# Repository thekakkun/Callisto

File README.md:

# Callisto

Callisto is a digital clock that uses a Russian IV-18 vacuum fluorescent tube for the display. The clock uses an ESP32 to automatically sync time.

The name *Callisto* was chosen so that the name could be displayed on an 8-digit seven-segment display.

## Features:
- Sync time, retrieved using WiFi
- Automatically switch to daylight saving time
- Clock display settings configured using web browser
- Automatic shutoff during night hours in order to decrease energy usage and extend tube life
- Auto-dimming based on ambient light conditions

## Special thanks

The software and hardware design of the clock was ~~stolen from~~ heavily inspired by the following projects:

- [Ice Tube Clock by Lady Ada](https://learn.adafruit.com/ice-tube-clock-kit/)
- [Flora-ESP8266 by mcer12](https://github.com/mcer12/Flora-ESP8266)

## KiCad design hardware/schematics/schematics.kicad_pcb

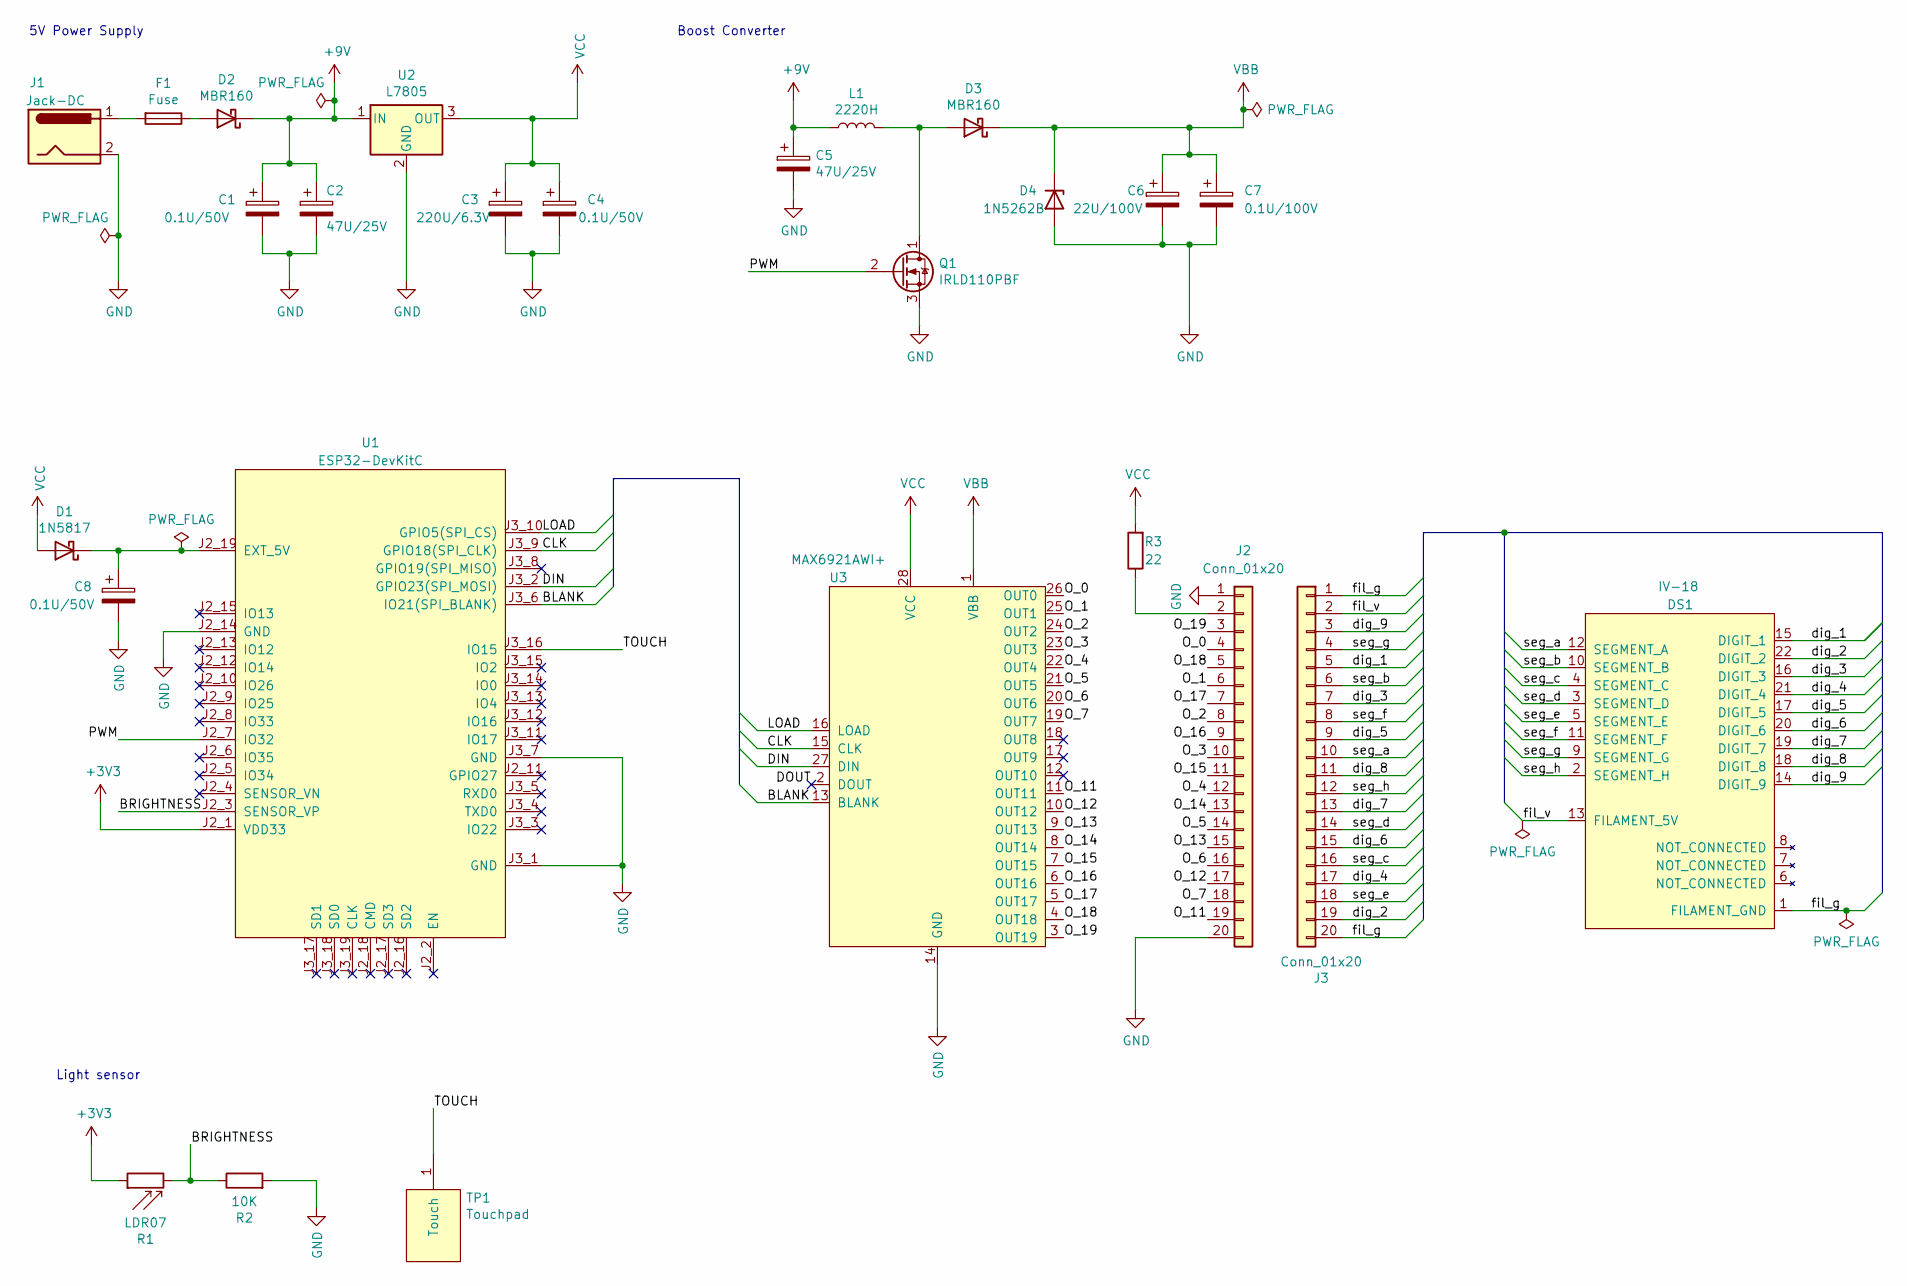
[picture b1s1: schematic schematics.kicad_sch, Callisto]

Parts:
C1, C4, C8: 0.1U/50V; C_Disc_D3.0mm_W1.6mm_P2.50mm
C2, C5: 47U/25V; CP_Radial_D5.0mm_P2.50mm
C3: 220U/6.3V; CP_Radial_D6.3mm_P2.50mm
C6: 22U/100V; CP_Radial_D6.3mm_P2.50mm
C7: 0.1U/100V; C_Disc_D3.0mm_W1.6mm_P2.50mm
D1: 1N5817; D_DO-41_SOD81_P10.16mm_Horizontal
D2, D3: MBR160; D_DO-41_SOD81_P10.16mm_Horizontal
D4: 1N5262B; D_DO-41_SOD81_P10.16mm_Horizontal
DS1: IV-18
F1: Fuse; Fuse_Littelfuse_395Series
J1: Jack-DC; BarrelJack_Horizontal
J2, J3: Conn_01x20; IDC-Header_2x10_P2.54mm_Vertical
L1: 2220H; L_Radial_D9.5mm_P5.00mm_Fastron_07HVP
Q1: IRLD110PBF; Vishay_HVM-DIP-3_W7.62mm
R1: LDR07; PinHeader_1x02_P2.54mm_Vertical
R2: 10K; R_Axial_DIN0207_L6.3mm_D2.5mm_P10.16mm_Horizontal
R3: 22; R_Axial_DIN0207_L6.3mm_D2.5mm_P10.16mm_Horizontal
TP1: Touchpad; PinHeader_1x01_P2.54mm_Vertical
U1: ESP32-DevKitC; ESP32 DevKitC
U2: L7805; L7805_with_heatsink
U3: MAX6921AWI+; SOIC-28W_7.5x17.9mm_P1.27mm

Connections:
+3V3: R1.1, U1.J2_1 (VDD33)
+9V: C1.1, C2.1, C5.1, D2.1 (K), L1.1, U2.1 (IN); also elsewhere on the board
/BLANK: U1.J3_6 (IO21(SPI_BLANK)), U3.13 (BLANK)
/BRIGHTNESS: R1.2, R2.1, U1.J2_3 (SENSOR_VP)
/CLK: U1.J3_9 (GPIO18(SPI_CLK)), U3.15 (CLK)
/DIN: U1.J3_2 (GPIO23(SPI_MOSI)), U3.27 (DIN)
/DOUT: U3.2 (DOUT)
/LOAD: U1.J3_10 (GPIO5(SPI_CS)), U3.16 (LOAD)
/O_0: J2.4, U3.26 (OUT0)
/O_1: J2.6, U3.25 (OUT1)
/O_2: J2.8, U3.24 (OUT2)
/O_3: J2.10, U3.23 (OUT3)
/O_4: J2.12, U3.22 (OUT4)
/O_5: J2.14, U3.21 (OUT5)
/O_6: J2.16, U3.20 (OUT6)
/O_7: J2.18, U3.19 (OUT7)
/O_11: J2.19, U3.11 (OUT11)
/O_12: J2.17, U3.10 (OUT12)
/O_13: J2.15, U3.9 (OUT13)
/O_14: J2.13, U3.8 (OUT14)
/O_15: J2.11, U3.7 (OUT15)
/O_16: J2.9, U3.6 (OUT16)
/O_17: J2.7, U3.5 (OUT17)
/O_18: J2.5, U3.4 (OUT18)
/O_19: J2.3, U3.3 (OUT19)
/PWM: Q1.2 (G), U1.J2_7 (IO32)
/TOUCH: TP1.1, U1.J3_16 (IO15)
/dig_1: DS1.15 (DIGIT_1), J3.5
/dig_2: DS1.22 (DIGIT_2), J3.19
/dig_3: DS1.16 (DIGIT_3), J3.7
/dig_4: DS1.21 (DIGIT_4), J3.17
/dig_5: DS1.17 (DIGIT_5), J3.9
/dig_6: DS1.20 (DIGIT_6), J3.15
/dig_7: DS1.19 (DIGIT_7), J3.13
/dig_8: DS1.18 (DIGIT_8), J3.11
/dig_9: DS1.14 (DIGIT_9), J3.3
/fil_g: DS1.1 (FILAMENT_GND), J3.1, J3.20
/fil_v: DS1.13 (FILAMENT_5V), J3.2
/seg_a: DS1.12 (SEGMENT_A), J3.10
/seg_b: DS1.10 (SEGMENT_B), J3.6
/seg_c: DS1.4 (SEGMENT_C), J3.16
/seg_d: DS1.3 (SEGMENT_D), J3.14
/seg_e: DS1.5 (SEGMENT_E), J3.18
/seg_f: DS1.11 (SEGMENT_F), J3.8
/seg_g: DS1.9 (SEGMENT_G), J3.4
/seg_h: DS1.2 (SEGMENT_H), J3.12
GND: C1.2, C2.2, C3.2, C4.2, C5.2, C6.2, C7.2, C8.2, D4.2 (A), J1.2, J2.1, J2.20, Q1.3 (S), R2.2, U1.J2_14 (GND), U1.J3_1 (GND), U1.J3_7 (GND), U2.2 (GND), U3.14 (GND)
unnamed: C8.1, D1.1 (K), U1.J2_19 (EXT_5V)
unnamed: D2.2 (A), F1.1
unnamed: D3.2 (A), L1.2, Q1.1 (D)
unnamed: F1.2, J1.1
unnamed: J2.2, R3.1
VBB: C6.1, C7.1, D3.1 (K), D4.1 (K), U3.1 (VBB); also elsewhere on the board
VCC: C3.1, C4.1, D1.2 (A), R3.2, U2.3 (OUT), U3.28 (VCC); also elsewhere on the board

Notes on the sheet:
5V Power Supply
Light sensor
Boost Converter

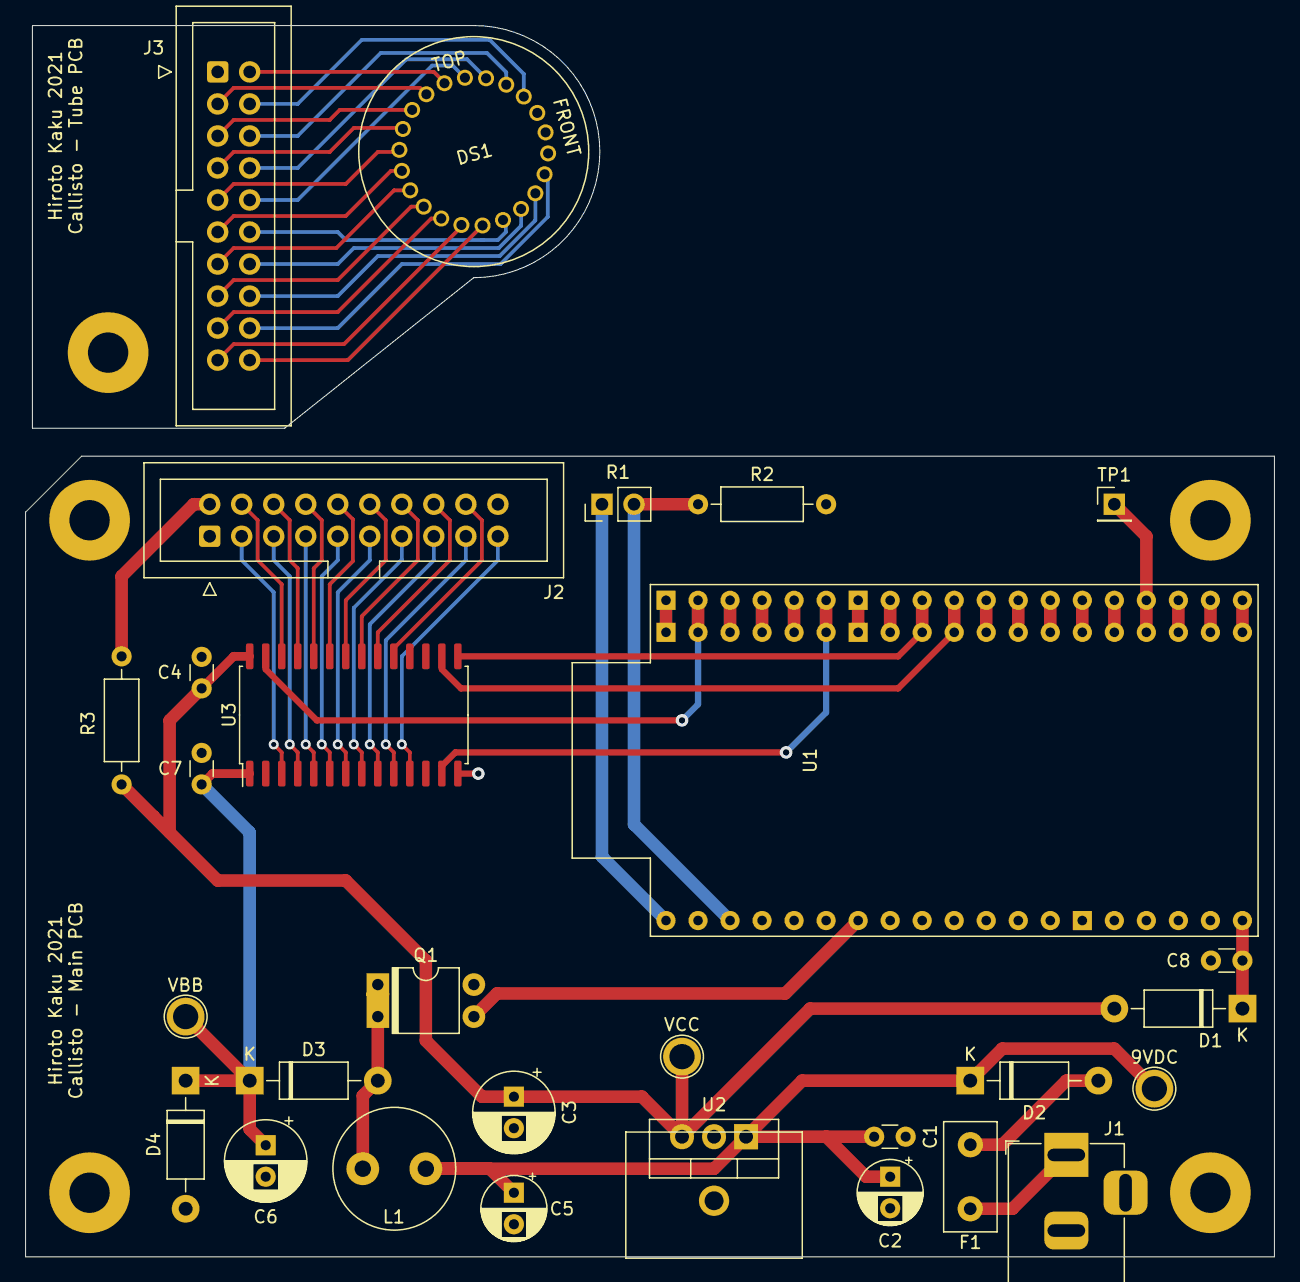
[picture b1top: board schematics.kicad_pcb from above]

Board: 2 copper layers, 99.1 x 97.7 mm, 29 parts (0 on the bottom side), 53 nets.

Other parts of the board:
9VDC: TestPoint_Plated_Hole_D2.0mm
VBB: TestPoint_Plated_Hole_D2.0mm
VCC: TestPoint_Plated_Hole_D2.0mm

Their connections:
+9V: 9VDC.1; also elsewhere on the board
VBB: VBB.1; also elsewhere on the board
VCC: VCC.1; also elsewhere on the board

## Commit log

2021-08-01 Datasheets moved to hardware folder
2021-08-01 Readme updated
2021-08-02 gitignore updated
2021-08-02 Config page and preferences feature completed
2021-08-02 .gitignore is now working
2021-08-02 Preferences cancel button implemented
2021-08-02 date and time display formats implemented
2021-08-03 night mode implemented
2021-08-03 Brightness uninverted, user settable
2021-08-03 get_mode logic cleaned up
2021-08-04 Brightness range set
2021-08-04 KiCad files added
2021-08-04 Implement brightness range damper
2021-08-04 5 power supply schematics drawn
2021-08-04 Boost converter schematic created
2021-08-06 Power management enabled
2021-08-06 Schematic footprints created
2021-08-08 Change flags to bool type
2021-08-09 Touch sensor fixed
2021-08-09 Schematics completed
2021-08-11 Main PCB completed
2021-08-16 Tube PCB wired
2021-08-17 Tube PCB created
2021-08-24 Capacitor placements tweaked
2021-08-30 PCB finalized
2021-08-30 Create font table based on MAX6921 pinout
2021-08-30 Gerber output folder renamed
2021-08-30 Gerber files moved to out folder
2021-08-30 Settings class in separate file
2021-09-01 Deep sleep during night, instead of just turning display off
2021-09-01 Comments added to function
2021-09-02 Show list of SSIDs on initial setup
2021-09-02 better defaults for brightness range
2021-09-07 Functions split into separate files
2021-09-07 Launch AP from main loop, like server
2021-09-08 Mesh files for case created
2021-09-15 Variable declaration moved outside of case labels
2021-09-15 ESP32 drill holes widened, display angle set to 15
2021-09-20 Manual created
2021-09-26 Wiring fixed
2021-09-26 Add to gitignore
2021-09-26 Updated based on c++ best practices
2021-09-29 Revision 2 of PCB, hopefully without workarounds
2021-10-05 Create a bit more space for tube board header
2021-10-19 Manual updated in Word
2021-10-19 Brightness based on duty cycle (cleaner math)
2021-10-20 Update blank input to PWM
2021-10-20 Cleared up to-dos
2021-10-25 Added moving average for LDR, brightness fixed
2021-10-28 Deep sleep wake-up fixed
2021-10-28 Default brightness change fixed
2021-10-29 Night mode fixed more
2021-10-30 Touch to wake time starts after wifi success
2021-11-01 Made more robust against wifi connection errors
2021-11-01 test code deleted
2021-11-03 Retain data when going to sleep
2021-11-04 Made factory reset work consistently
2021-11-04 Run brightness range damper on wake
2021-11-06 Start wifi if entering config during night
2021-11-08 Note about time inaccuracies during night mode
2021-11-09 Turned off autocapitalize for wifi name
2021-11-12 Manual proofread
2021-11-12 Punctuation fixed
2021-12-30 Update README.md
    Photo added
2021-12-30 updated to KiCad 6
2021-12-30 PDFs added for easy viewing of PCB design
2021-12-30 color palette changed to show labels
2022-01-04 links in pdf now work
2022-02-10 added CAD file
2022-02-10 add features to introduction
2022-04-28 Fix typo
2024-07-27 Fix outdated imports
2024-07-27 Remove linter workaround
